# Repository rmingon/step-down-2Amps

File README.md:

# Step-Down 2A Buck Regulator

## Overview

- Compact synchronous buck converter built around the TI `TPS562200`, delivering a regulated 3.3 V rail at up to 2 A continuous load.
- Intended as a drop-in power stage for embedded projects that need to step 4.5-17 V sources (battery packs, adapters, backplanes) down to logic-level supplies.
- Three-pin interface exposes the regulated output, return, and raw input for easy wiring or header mounting.

## Electrical Data

- **Input voltage:** 4.5-17 V (per `TPS562200` operating range)
- **Nominal output:** 3.3 V (set by the 33 kOhm / 10 kOhm feedback divider)
- **Continuous current:** up to 2 A with adequate airflow and low-loss layout
- **Switching frequency:** 580 kHz (fixed by controller)

### Pinout (`J1`, from silkscreen Pin 1 marker toward Pin 3)

| Pin | Net  | Function                            |
| --- | ---- | ----------------------------------- |
| 1   | +3V3 | Regulated 3.3 V output              |
| 2   | GND  | Power ground / return               |
| 3   | VCC  | Raw input voltage (also feeds `EN`) |

## Repository Contents

- `hardware.kicad_sch`, `hardware.kicad_pcb`: KiCad 8 project files for schematic and board layout.
- `pcb.png`, `3d.png`, `schematic.png`: Quick references for the layout, render, and top-level schematic.

## Assembly Notes

- All passives are 0603 packages.
- `EN` is permanently tied high through the resistor divider, so the regulator starts when `VCC` is present.
- Populate at least one of the 22 uF output capacitors (`C11`, `C12`) for stability; both footprints can be stuffed for additional bulk capacitance.

## Using the Board

1. Solder the three-pin header or wire leads to `J1`.
2. Apply your input source to `VCC`/`GND` and confirm the 3.3 V output on `+3V3`.
3. For different output voltages, adjust the feedback divider (`R14` high-side, `R13` low-side) per the `TPS562200` datasheet (Vout = 0.765 V \* (1 + R14 / R13)).

## License

- Released under the CERN Open Hardware Licence Version 2 - Permissive (`CERN-OHL-P v2`). See `LICENSE` for the full terms and obligations when using the design or producing hardware from it.

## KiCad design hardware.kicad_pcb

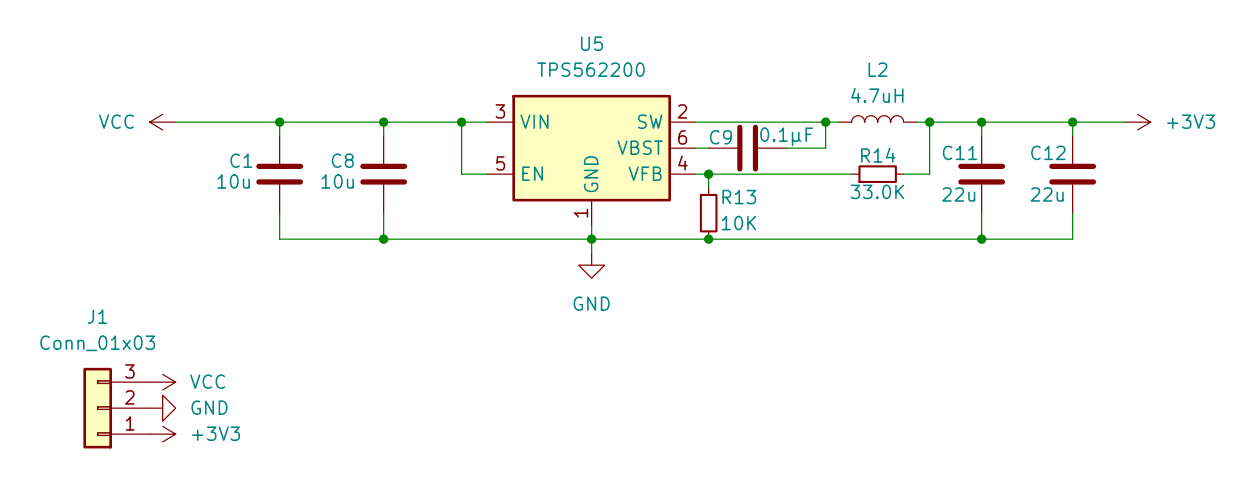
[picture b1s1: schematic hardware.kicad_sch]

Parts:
C1, C8: 10u; C_0603_1608Metric; LCSC C1691
C9: 0.1µF; C_0603_1608Metric; LCSC C6119867
C11, C12: 22u; C_0603_1608Metric; LCSC C6119867
J1: Conn_01x03; PinHeader_1x03_P2.54mm_Vertical
L2: 4.7uH; L_Chilisin_BMRA00050520; LCSC C3002619
R13: 10K; R_0603_1608Metric; LCSC C25804
R14: 33.0K; R_0603_1608Metric; LCSC C4216
U5: TPS562200; SOT-23-6; LCSC C49757

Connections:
+3V3: C11.1, C12.1, J1.1, L2.2, R14.2
GND: C1.2, C8.2, C11.2, C12.2, J1.2, R13.2, U5.1 (GND)
unnamed: C9.2, L2.1, U5.2 (SW)
unnamed: C9.1, U5.6 (VBST)
unnamed: R13.1, R14.1, U5.4 (VFB)
VCC: C1.1, C8.1, J1.3, U5.3 (VIN), U5.5 (EN)

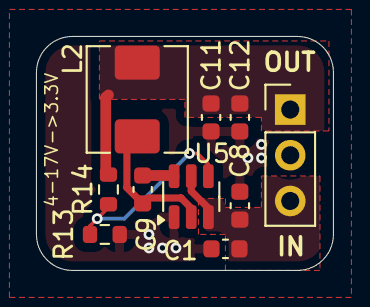
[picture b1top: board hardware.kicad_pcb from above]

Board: 2 copper layers, 16.5 x 13.0 mm, 10 parts (0 on the bottom side), 6 nets.

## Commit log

2025-11-02 add wiring schematic + pcb
2025-11-02 add pictures
2025-11-02 add readme
2025-11-02 add license
2025-11-02 remove unused readme info
